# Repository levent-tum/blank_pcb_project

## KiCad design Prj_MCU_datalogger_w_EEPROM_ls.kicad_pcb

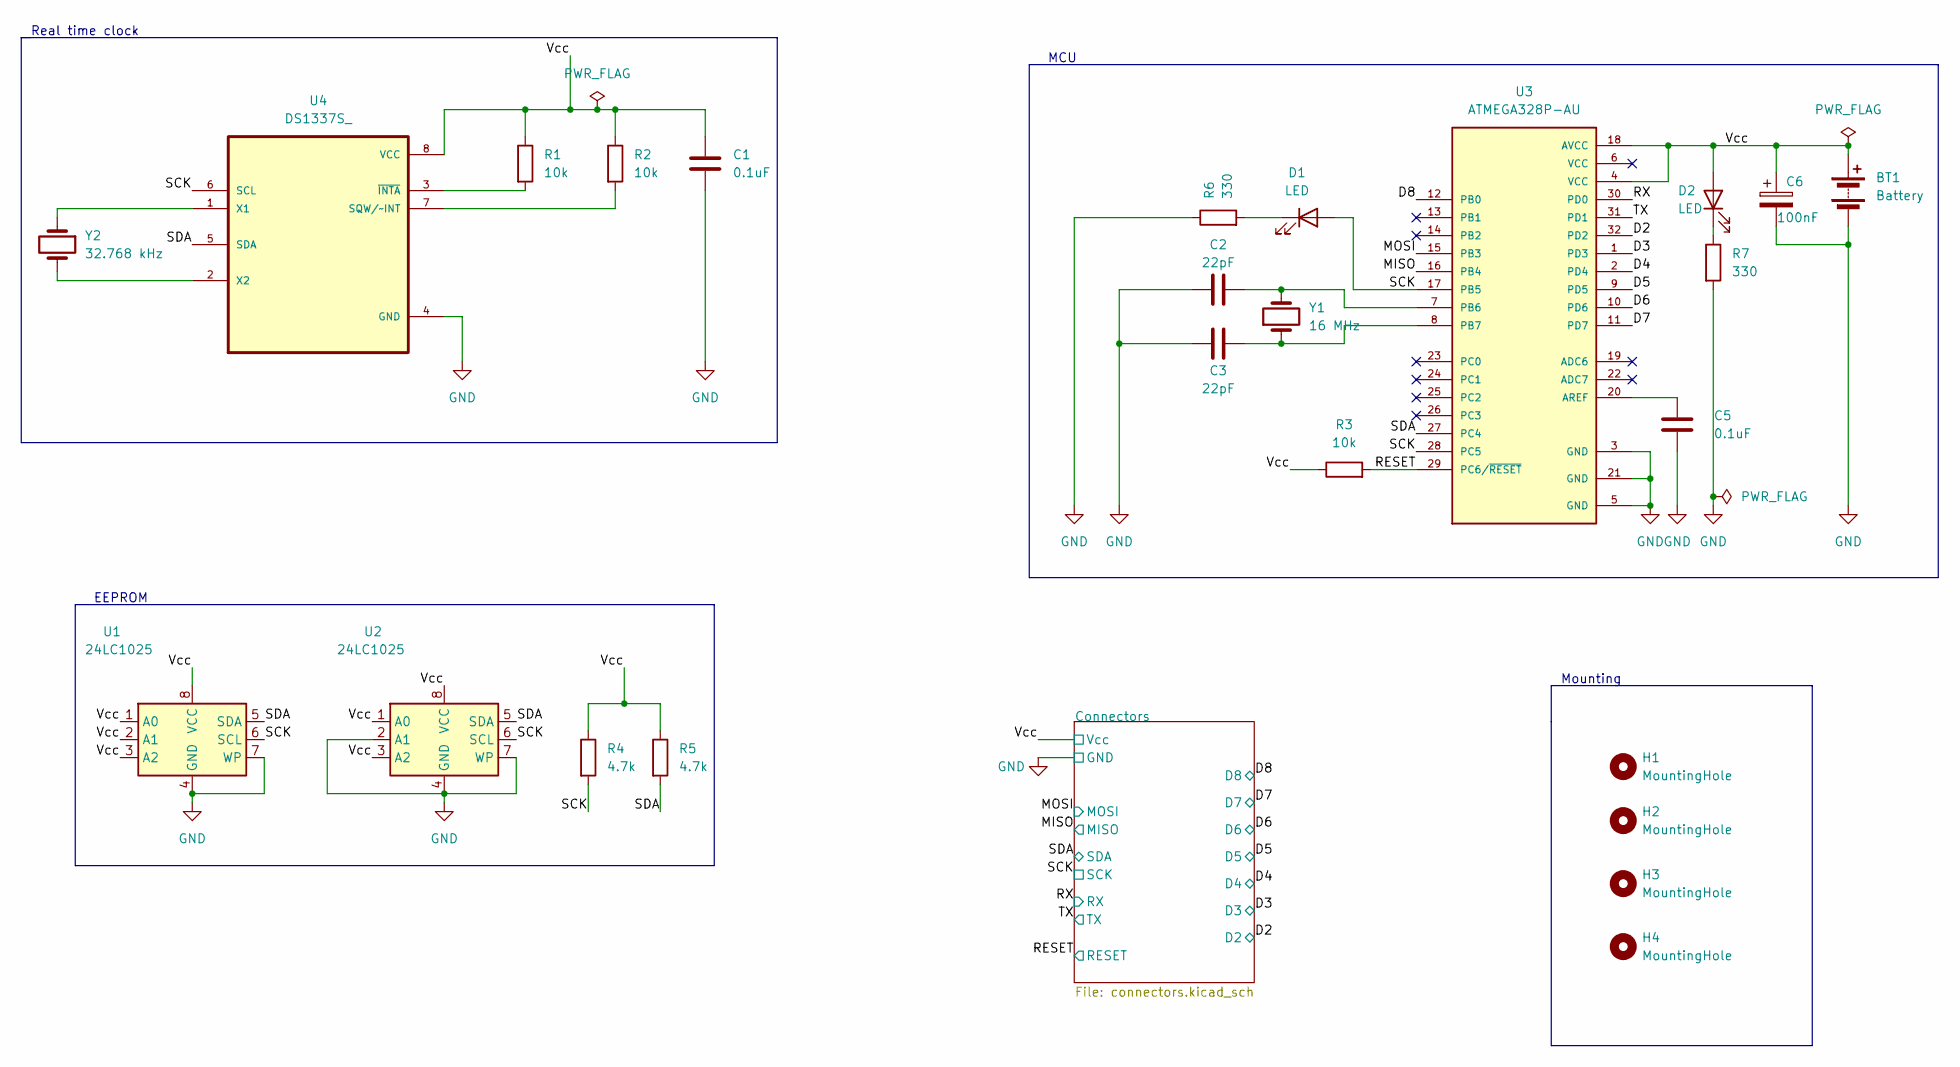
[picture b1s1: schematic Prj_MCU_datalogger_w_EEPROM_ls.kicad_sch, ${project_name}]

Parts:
BT1: Battery; PinHeader_1x02_P2.54mm_Vertical
C1, C5: 0.1uF; C_0805_2012Metric
C2, C3: 22pF; C_0805_2012Metric
C6: 100nF; C_0805_2012Metric
D1, D2: LED; LED_0805_2012Metric
H1, H2, H3, H4: MountingHole; MountingHole_2.1mm
R1, R2, R3: 10k; R_0805_2012Metric
R4, R5: 4.7k; R_0805_2012Metric
R6, R7: 330; R_0805_2012Metric
U1, U2: 24LC1025; SOIC-8_5.23x5.23mm_P1.27mm
U3: ATMEGA328P-AU; QFP80P900X900X120-32N; PARTREV 8271A
U4: DS1337S_; SOIC127P600X175-8N
Y1: 16 MHz; Crystal_SMD_5032-2Pin_5.0x3.2mm_HandSoldering
Y2: 32.768 kHz; Crystal_SMD_5032-2Pin_5.0x3.2mm_HandSoldering

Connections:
/D2: U3.32 (PD2); also elsewhere on the board
/D3: U3.1 (PD3); also elsewhere on the board
/D4: U3.2 (PD4); also elsewhere on the board
/D5: U3.9 (PD5); also elsewhere on the board
/D6: U3.10 (PD6); also elsewhere on the board
/D7: U3.11 (PD7); also elsewhere on the board
/D8: U3.12 (PB0); also elsewhere on the board
/MISO: U3.16 (PB4); also elsewhere on the board
/MOSI: U3.15 (PB3); also elsewhere on the board
/RESET: R3.2, U3.29 (PC6/~RESET); also elsewhere on the board
/RX: U3.30 (PD0); also elsewhere on the board
/SCK: D1.2 (A), R4.2, U1.6 (SCL), U2.6 (SCL), U3.17 (PB5), U3.28 (PC5), U4.6 (SCL); also elsewhere on the board
/SDA: R5.2, U1.5 (SDA), U2.5 (SDA), U3.27 (PC4), U4.5 (SDA); also elsewhere on the board
/TX: U3.31 (PD1); also elsewhere on the board
/Vcc: BT1.1 (+), C1.1, C6.1, D2.2 (A), R1.1, R2.1, R3.1, R4.1, R5.1, U1.1 (A0), U1.2 (A1), U1.3 (A2), U1.8 (VCC), U2.1 (A0), U2.3 (A2), U2.8 (VCC), U3.4 (VCC), U3.18 (AVCC), U4.8 (VCC); also elsewhere on the board
GND: BT1.2 (-), C1.2, C2.1, C3.1, C5.1, C6.2, R6.1, R7.2, U1.4 (GND), U1.7 (WP), U2.2 (A1), U2.4 (GND), U2.7 (WP), U3.3 (GND), U3.5 (GND), U3.21 (GND), U4.4 (GND); also elsewhere on the board
unnamed: D1.1 (K), R6.2
unnamed: D2.1 (K), R7.1
unnamed: C5.2, U3.20 (AREF)
unnamed: C2.2, U3.7 (PB6), Y1.2
unnamed: C3.2, U3.8 (PB7), Y1.1
unnamed: R2.2, U4.7 (SQW/~INT)
unnamed: U4.1 (X1), Y2.1
unnamed: U4.2 (X2), Y2.2
unnamed: R1.2, U4.3 (~INTA)

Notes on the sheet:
Real time clock
Mounting
EEPROM
MCU

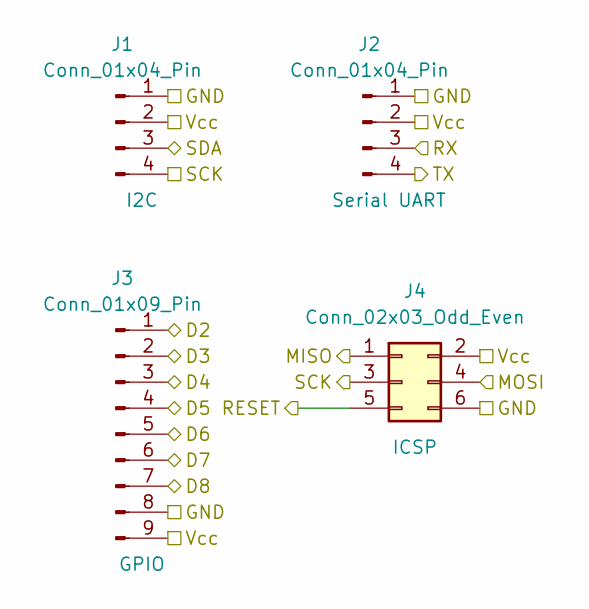
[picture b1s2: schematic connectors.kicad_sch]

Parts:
J1, J2: Conn_01x04_Pin; PinHeader_1x04_P2.54mm_Vertical
J3: Conn_01x09_Pin; PinHeader_1x09_P2.54mm_Vertical
J4: Conn_02x03_Odd_Even; PinHeader_2x03_P2.54mm_Vertical

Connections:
/D2: J3.1; also elsewhere on the board
/D3: J3.2; also elsewhere on the board
/D4: J3.3; also elsewhere on the board
/D5: J3.4; also elsewhere on the board
/D6: J3.5; also elsewhere on the board
/D7: J3.6; also elsewhere on the board
/D8: J3.7; also elsewhere on the board
/MISO: J4.1; also elsewhere on the board
/MOSI: J4.4; also elsewhere on the board
/RESET: J4.5; also elsewhere on the board
/RX: J2.3; also elsewhere on the board
/SCK: J1.4, J4.3; also elsewhere on the board
/SDA: J1.3; also elsewhere on the board
/TX: J2.4; also elsewhere on the board
/Vcc: J1.2, J2.2, J3.9, J4.2; also elsewhere on the board
GND: J1.1, J2.1, J3.8, J4.6; also elsewhere on the board

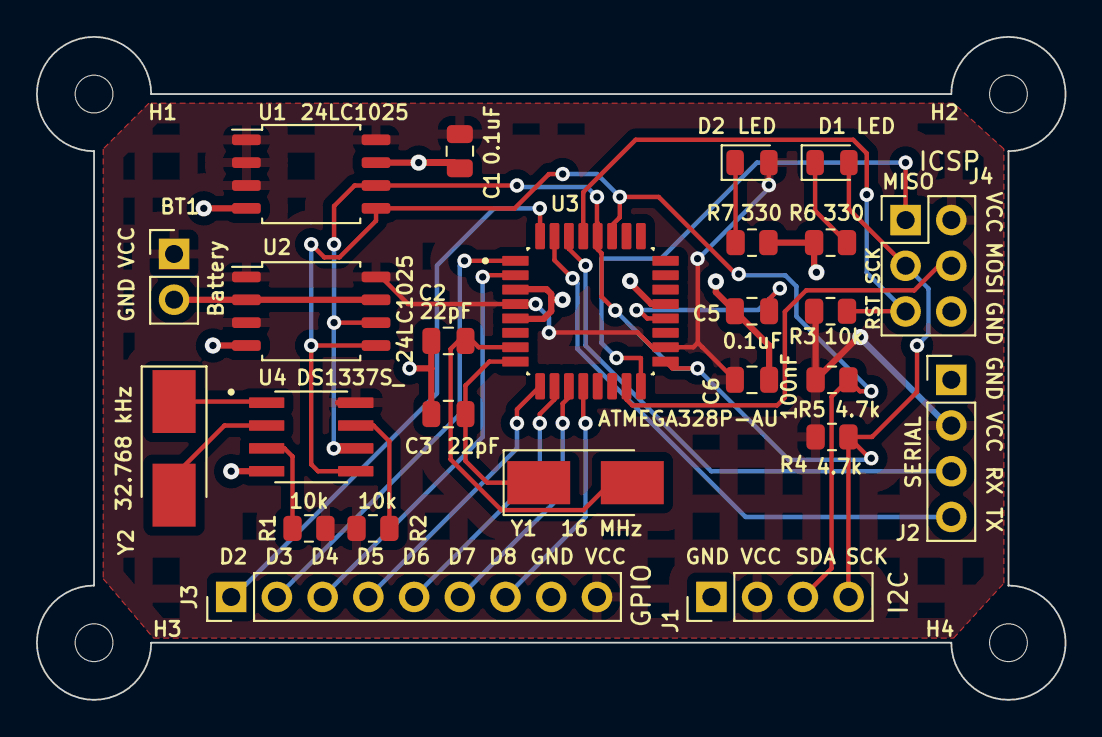
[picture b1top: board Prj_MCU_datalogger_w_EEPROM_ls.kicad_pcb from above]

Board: 2 copper layers, 57.1 x 36.8 mm, 29 parts (0 on the bottom side), 25 nets.

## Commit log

2023-12-11 First commit of new project.
2023-12-11 Setup of EESCHEMA
2023-12-11 Have added required symbols to the schematic sheets.
2023-12-11 Changed locations of symbols (arrange)
2023-12-11 Added component values.
2023-12-12 Completed symbol-footprint associations.
2023-12-12 Completed wiring of main sheet.
2023-12-12 Completed wiring of secondary sheet.
2023-12-12 Allocated GND and Vcc nets to the Power net class.
2023-12-12 Completed comments.
2023-12-12 Setup Pcbnew.
2023-12-13 Completed placement of footprints
2023-12-13 Routing sans GND completed
2023-12-13 Completed routing
2023-12-13 Refined routing
2023-12-13 Refined routing.v2
2023-12-13 Refined routing.v3
2023-12-13 Refined routing.v4
2023-12-13 Fixed issues
2023-12-13 Completed 2-layer PCB project
2023-12-13 Completed 2-layer PCB project_3dmodels
2023-12-14 Added gerber directories to git ignore
2023-12-14 Added gittatributes file to ignore PCB files during merge
2023-12-14 Made small change to schematic.
2023-12-14 Added gitattributes file to prevent PCB files from merge
2023-12-14 test label change
2023-12-15 Fixed two defects in the schematic.
2023-12-15 4-layer board
